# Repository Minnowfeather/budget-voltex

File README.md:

# Budget Voltex

A DIY PCB aiming to be as cheap to produce as possible, while not compromising on comfort and usability.

# Requirements

- 3D Printer (256x256 bed)

# BOM

| Qty | Part              | Link |
| --- | ----------------- | ---- |
| 1   | Raspberry Pi Pico | tbd  |

# ToDo

**V2**

- [ ] LED support
- [x] Migrate to choc/omni switch footprint
- [ ] Any bugfixes

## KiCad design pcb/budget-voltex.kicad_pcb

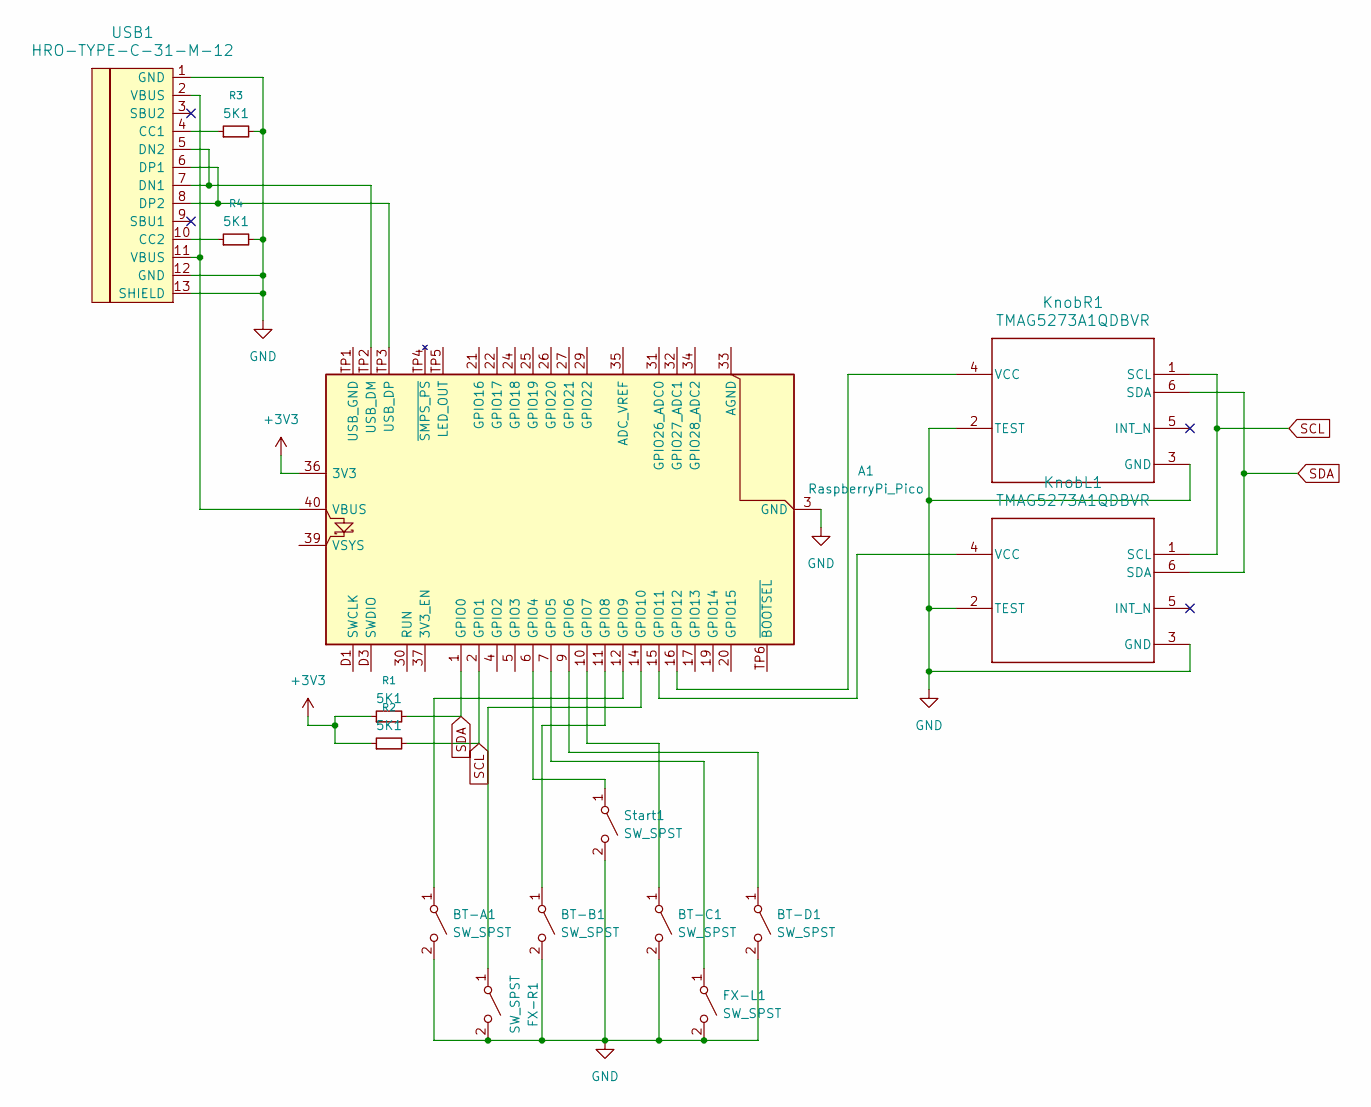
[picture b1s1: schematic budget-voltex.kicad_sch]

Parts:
A1: RaspberryPi_Pico; RaspberryPi_Pico_SMD_Modified
BT-A1: SW_SPST; SW_PG1350
BT-B1: SW_SPST; SW_PG1350
BT-C1: SW_SPST; SW_PG1350
BT-D1: SW_SPST; SW_PG1350
FX-L1: SW_SPST; SW_PG1350
FX-R1: SW_SPST; SW_PG1350
KnobL1: TMAG5273A1QDBVR; DBV0006A-IPC_A
KnobR1: TMAG5273A1QDBVR; DBV0006A-IPC_A
R1, R2, R3, R4: 5K1; R_0603_1608Metric_Pad0.98x0.95mm_HandSolder
Start1: SW_SPST; SW_PG1350
USB1: HRO-TYPE-C-31-M-12; HRO-TYPE-C-31-M-12-HandSoldering

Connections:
+3V3: A1.36 (3V3), R1.1, R2.1
GND: A1.3 (GND), A1.8 (GND), A1.13 (GND), A1.18 (GND), A1.23 (GND), A1.28 (GND), A1.38 (GND), A1.D2 (GND), BT-A1.2 (B), BT-B1.2 (B), BT-C1.2 (B), BT-D1.2 (B), FX-L1.2 (B), FX-R1.2 (B), KnobL1.2 (TEST), KnobL1.3 (GND), KnobR1.2 (TEST), KnobR1.3 (GND), R3.2, R4.2, Start1.2 (B), USB1.1 (GND), USB1.12 (GND), USB1.13 (SHIELD)
unnamed: A1.6 (GPIO4), Start1.1 (A)
unnamed: A1.7 (GPIO5), FX-L1.1 (A)
unnamed: A1.9 (GPIO6), BT-D1.1 (A)
unnamed: A1.10 (GPIO7), BT-C1.1 (A)
unnamed: A1.11 (GPIO8), BT-B1.1 (A)
unnamed: A1.12 (GPIO9), BT-A1.1 (A)
unnamed: A1.14 (GPIO10), FX-R1.1 (A)
unnamed: A1.15 (GPIO11), KnobL1.4 (VCC)
unnamed: A1.16 (GPIO12), KnobR1.4 (VCC)
unnamed: A1.TP2 (USB_DM), USB1.5 (DN2), USB1.7 (DN1)
unnamed: A1.TP3 (USB_DP), USB1.6 (DP1), USB1.8 (DP2)
unnamed: A1.40 (VBUS), USB1.2 (VBUS), USB1.11 (VBUS)
unnamed: R3.1, USB1.4 (CC1)
unnamed: R4.1, USB1.10 (CC2)
SCL: A1.2 (GPIO1), KnobL1.1 (SCL), KnobR1.1 (SCL), R2.2
SDA: A1.1 (GPIO0), KnobL1.6 (SDA), KnobR1.6 (SDA), R1.2

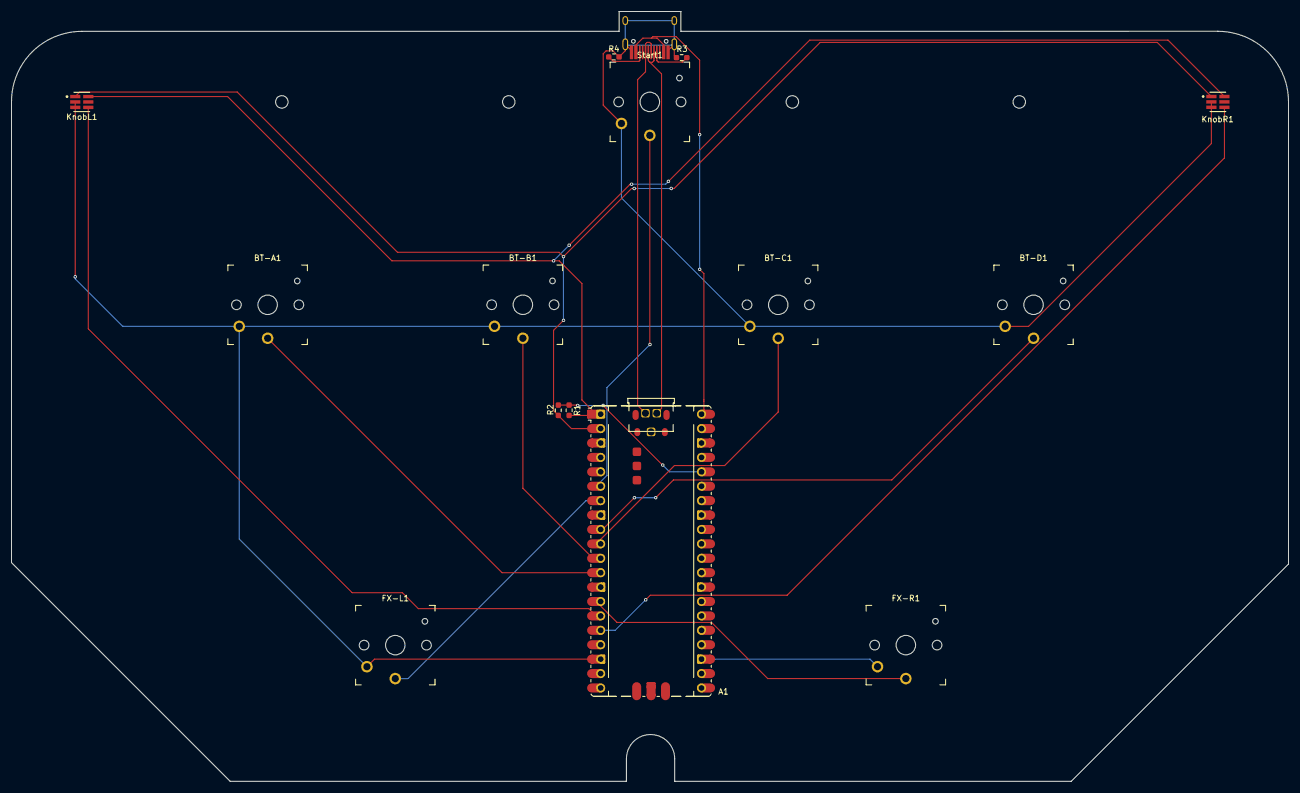
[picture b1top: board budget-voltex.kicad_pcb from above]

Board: 2 copper layers, 225.1 x 135.7 mm, 15 parts (0 on the bottom side), 18 nets.

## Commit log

2025-12-09 init
2025-12-09 restructure
2025-12-09 put elements on pcb
2025-12-10 finish schematic, finish wiring for pcb
2025-12-14 update wiring/schematic, shape pcb
2025-12-14 remove redundant wires, export gerber
2026-02-03 Updated key footprints to use chocs, rewire everything
2026-03-09 Fix positioning of fx buttons
2026-04-26 Idk what i did
2026-04-26 Fix clearance violations
